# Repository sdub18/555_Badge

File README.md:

# 555_Badge
An electronic Badge Design

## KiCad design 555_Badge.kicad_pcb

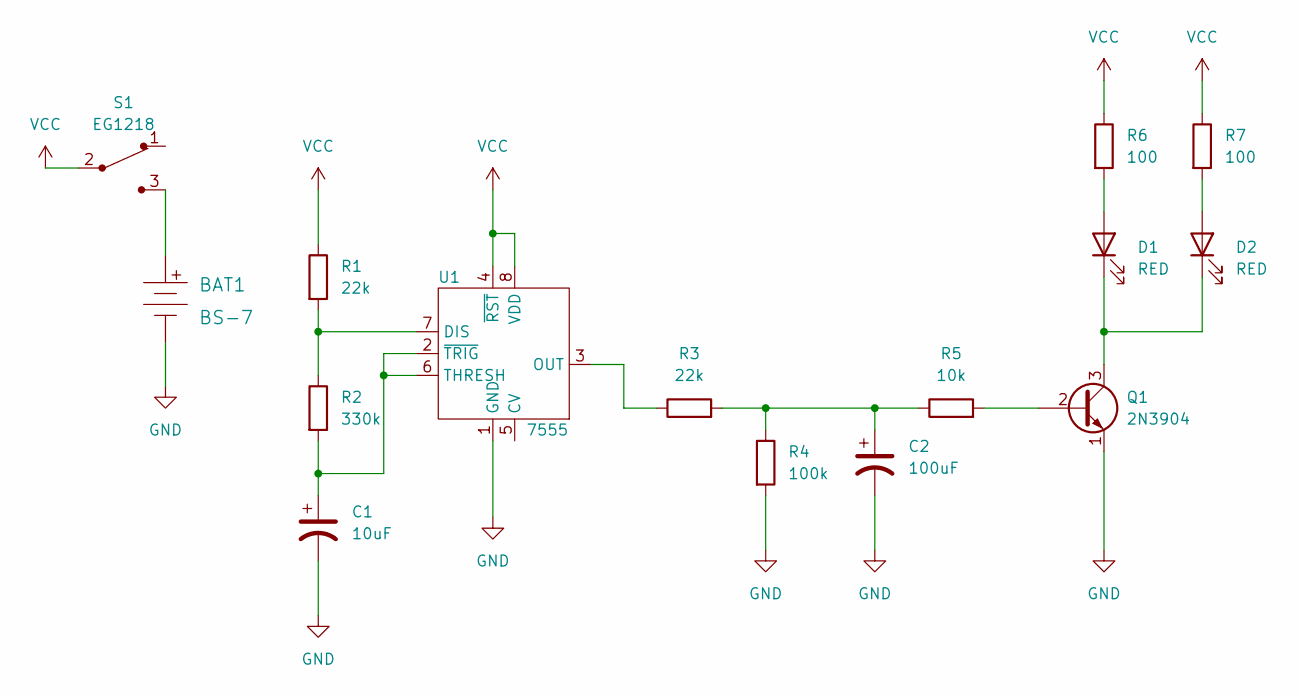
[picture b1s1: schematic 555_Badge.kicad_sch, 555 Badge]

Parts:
BAT1: BS-7; Battery_Holder_Coin_2032_BS-7; MPN BS-7; Digi-Key_PN BS-7-ND
C1: 10uF; CP_Radial_D5.0mm_P2.00mm
C2: 100uF; CP_Radial_D6.3mm_P2.50mm
D1, D2: RED; LED_D3.0mm
Q1: 2N3904; TO-92-3
R1, R3: 22k; R_Axial_DIN0207_L6.3mm_D2.5mm_P7.62mm_Horizontal
R2: 330k; R_Axial_DIN0207_L6.3mm_D2.5mm_P7.62mm_Horizontal
R4: 100k; R_Axial_DIN0207_L6.3mm_D2.5mm_P7.62mm_Horizontal
R5: 10k; R_Axial_DIN0207_L6.3mm_D2.5mm_P7.62mm_Horizontal
R6, R7: 100; R_Axial_DIN0207_L6.3mm_D2.5mm_P7.62mm_Horizontal
S1: EG1218; Switch_Slide_11.6x4mm_EG1218; MPN EG1218; Digi-Key_PN EG1903-ND
U1: 7555; ICM7555-PDIP

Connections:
GND: BAT1.Neg, C1.2, C2.2, Q1.1 (E), R4.2, U1.1 (GND)
unnamed: BAT1.Pos, S1.3
unnamed: C1.1, R2.2, U1.2 (~TRIG), U1.6 (THRESH)
unnamed: C2.1, R3.2, R4.1, R5.1
unnamed: D1.1 (K), D2.1 (K), Q1.3 (C)
unnamed: D1.2 (A), R6.2
unnamed: D2.2 (A), R7.2
unnamed: Q1.2 (B), R5.2
unnamed: R1.2, R2.1, U1.7 (DIS)
unnamed: R3.1, U1.3 (OUT)
VCC: R1.1, R6.1, R7.1, S1.2, U1.4 (~RST), U1.8 (VDD)

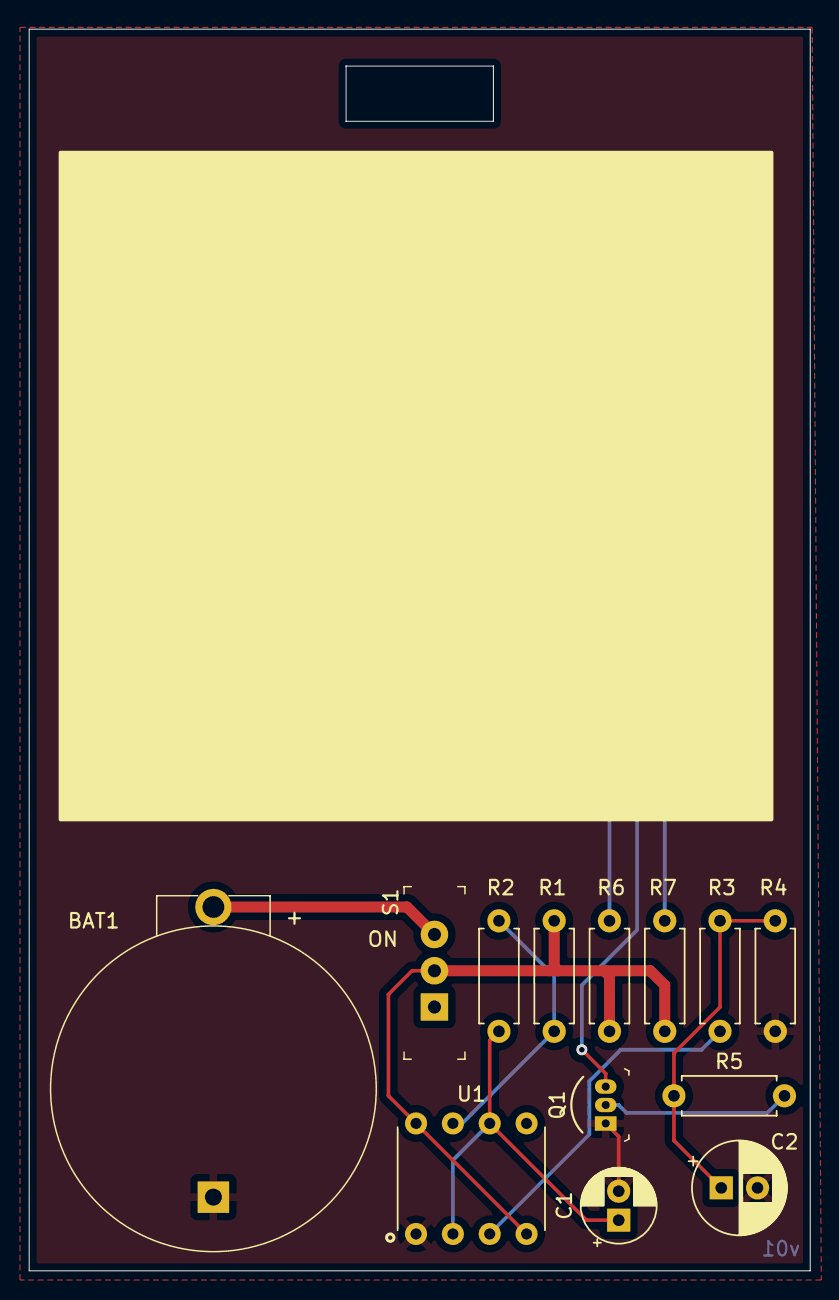
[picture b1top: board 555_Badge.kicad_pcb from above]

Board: 2 copper layers, 53.8 x 85.6 mm, 15 parts (0 on the bottom side), 11 nets.

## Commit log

2022-03-12 Initial Schematic and PCB files
2022-03-12 Created 555 Badge symbol
2022-03-12 Small changes to the badge symbol and finished schematic
2022-03-13 Created 555 Timer footprint for PCB
2022-03-13 More changes to schematic. Numbered all of my resistors and capacitors
2022-03-13 Lot of work on schematic and PCB to place components and begin constructing the PCB layout
2022-03-13 Everything looks amazing. PCB is basically done. Just need to generate a gerber file
2022-03-13 generated gerber files

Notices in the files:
555_Badge.kicad_pcb:
License CC BY 4.0
